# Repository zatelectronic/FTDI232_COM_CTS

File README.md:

<div align="center">

# FTDI232 COM CTS

**Conversor USB-Serial compacto com conector USB-C, chip FT232RL, seleção de tensão 3,3V / 5V, 3 LEDs de status e saída com pino CTS — totalmente SMD**

</div>

---

## 📋 Índice

- [FTDI232 COM CTS](#ftdi232-com-cts)
  - [📋 Índice](#-índice)
  - [Visão Geral](#visão-geral)
  - [Renders 3D](#renders-3d)
  - [Funcionalidades](#funcionalidades)
  - [Diagrama de Blocos](#diagrama-de-blocos)
  - [Especificações Técnicas](#especificações-técnicas)
  - [Lista de Materiais](#lista-de-materiais)
  - [Pinagem dos Conectores](#pinagem-dos-conectores)
    - [J2 — Saída Serial (6 pinos angulado)](#j2--saída-serial-6-pinos-angulado)
    - [JP1 — Seleção de Tensão](#jp1--seleção-de-tensão)
  - [Seleção de Tensão — JP1](#seleção-de-tensão--jp1)
  - [Aplicações](#aplicações)
  - [Estrutura do Repositório](#estrutura-do-repositório)
  - [Como Usar](#como-usar)
    - [Conexão com Arduino (programação)](#conexão-com-arduino-programação)
    - [Conexão com ESP8266 / ESP32](#conexão-com-esp8266--esp32)
    - [Instalação de drivers](#instalação-de-drivers)
  - [Sobre](#sobre)

---

## Visão Geral

**FTDI232 COM CTS** é um módulo conversor **USB para Serial (UART)** compacto e totalmente SMD, projetado pela **ZAT ELECTRONIC** utilizando **KiCad 10**. O módulo é baseado no chip **FT232RL** (SSOP-28), reconhecido automaticamente pelo sistema operacional sem necessidade de drivers adicionais na maioria das plataformas.

O diferencial deste módulo em relação a conversores convencionais é a presença do **pino CTS** no conector de saída de 6 pinos, além do tradicional conjunto **GND / VCC / TX / RX / DTR**. A tensão de saída é selecionável entre **3,3V e 5V** via jumper **(JP1)**, tornando o módulo compatível com uma ampla variedade de microcontroladores e módulos seriais. A entrada USB utiliza o conector **USB-C** (USB4105GFA SMD).

> 💡 Ideal para programação de Arduino bootloader, ESP8266, ESP32 sem USB nativo, módulos GSM, GPS e qualquer dispositivo com interface UART.

---

## Renders 3D

<div align="center">

*Vista superior — FT232RL SSOP-28, USB-C, LEDs SMD 0805, jumper JP1 e conector de 6 pinos com CTS*

<br/>

*Vista isométrica — layout compacto SMD com saída de 6 pinos angulada*

</div>

---

## Funcionalidades

- ✅ **Chip FT232RL** (SSOP-28 SMD) — conversor USB-Serial confiável e amplamente suportado
- ✅ **Conector USB-C** (USB4105GFA SMD) — entrada USB moderna e resistente
- ✅ **Seleção de tensão 3,3V / 5V** via jumper JP1 — compatível com diferentes lógicas
- ✅ **Pino CTS** disponível no conector de saída — diferencial para controle de fluxo
- ✅ **Pino DTR** disponível — reset automático de Arduino e bootloaders
- ✅ **3 LEDs SMD 0805** (L1, L2, L3) — indicação visual de TX, RX e alimentação
- ✅ **Diodo Schottky SS1P3L** (D1, DO-220AA SMD) — proteção na linha de alimentação VBUS
- ✅ **Capacitor eletrolítico 10µF/16V** (C1, EIA-3216 SMD) — filtragem da alimentação
- ✅ **Capacitores de desacoplamento 100nF e 1µF** (C2, C3, C4 — 0805 SMD)
- ✅ **Resistores de proteção e pull-up** (R1–R6 — 1206 SMD)
- ✅ **Layout totalmente SMD** — compacto e profissional
- ✅ **Saída por header de 6 pinos angulado** (J2) — encaixe direto em cabos e módulos

---

## Diagrama de Blocos

```
┌─────────────┐       ┌──────────────────┐       ┌─────────────────────────┐
│  USB-C      │       │   FT232RL        │       │  Conector J2 (6 pinos)  │
│ USB4105GFA  │──────►│   SSOP-28        │──────►│  GND                    │
│             │  USB  │                  │       │  CTS  ← diferencial     │
│  D+ / D-   │       │  TX / RX / DTR   │       │  VCC (3,3V ou 5V)       │
└─────────────┘       │  CTS / RTS       │       │  TX                     │
                      │  CBUS0 / CBUS1   │       │  RX                     │
                      └──────────────────┘       │  DTR                    │
                               │                 └─────────────────────────┘
                          [JP1 Jumper]
                        3,3V ●──○──● 5V
                        (seleção de tensão VCC)

         [L1] TX LED    [L2] RX LED    [L3] PWR LED  ← indicação visual
         [D1] Schottky SS1P3L ← proteção VBUS
```

---

## Especificações Técnicas

| Parâmetro | Valor |
|-----------|-------|
| **Chip conversor** | FT232RL (SSOP-28 SMD) |
| **Conector USB** | USB-C — USB4105GFA SMD |
| **Tensão de saída** | 3,3V ou 5V (selecionável via JP1) |
| **Interface serial** | UART — TX, RX, RTS, CTS, DTR |
| **Pinos disponíveis** | GND, CTS, VCC, TX, RX, DTR |
| **LEDs de status** | 3x SMD 0805 — TX (L1), RX (L2), PWR (L3) |
| **Diodo de proteção** | SS1P3L — Schottky (DO-220AA SMD) |
| **Capacitor principal** | 10µF / 16V (EIA-3216 SMD) |
| **Capacitores de desacoplamento** | 100nF e 1µF (0805 SMD) |
| **Resistores** | 0Ω, 1KΩ, 5,1KΩ (1206 SMD) |
| **Jumper de tensão** | JP1 — 3 pinos 2,54mm (header vertical) |
| **Conector de saída** | J2 — 6 pinos angulado 2,54mm (right angle) |
| **Tipo de montagem** | SMD |
| **Ferramenta de Projeto** | KiCad 10 |

---

## Lista de Materiais

| Ref | Componente | Valor / Parte | Encapsulamento |
|-----|-----------|--------------|----------------|
| U1 | Conversor USB-Serial | FT232RL | SSOP-28 SMD |
| J1 | Conector USB | USB-C (USB4105GFA) | SMD |
| J2 | Conector de Saída | 6 pinos — GND/CTS/VCC/TX/RX/DTR | Header angulado 2,54mm |
| JP1 | Jumper de Tensão | 3,3V / VCC / 5V | Header 3 pinos 2,54mm |
| D1 | Diodo Schottky | SS1P3L | DO-220AA SMD |
| L1 | LED TX | SMD 0805 | 0805 |
| L2 | LED RX | SMD 0805 | 0805 |
| L3 | LED PWR | SMD 0805 | 0805 |
| C1 | Capacitor Eletrolítico | 10µF / 16V | EIA-3216-18 SMD |
| C2, C3 | Capacitor de desacoplamento | 100nF | 0805 SMD |
| C4 | Capacitor de desacoplamento | 1µF / 50V | 0805 SMD |
| R1, R2 | Resistor | 0Ω (jumper) | 1206 SMD |
| R3, R4, R5 | Resistor de proteção | 1KΩ | 1206 SMD |
| R6 | Resistor pull-up | 5,1KΩ | 1206 SMD |

---

## Pinagem dos Conectores

### J2 — Saída Serial (6 pinos angulado)

| Pino | Sinal | Descrição |
|------|-------|-----------|
| 1 | GND | Terra |
| 2 | CTS | Clear To Send — controle de fluxo de hardware |
| 3 | VCC | Tensão de saída (3,3V ou 5V conforme JP1) |
| 4 | TX | Transmissão serial (saída do FT232RL) |
| 5 | RX | Recepção serial (entrada do FT232RL) |
| 6 | DTR | Data Terminal Ready — reset automático Arduino |

### JP1 — Seleção de Tensão

| Posição | Tensão VCC |
|---------|-----------|
| Pinos 1-2 | 3,3V |
| Pinos 2-3 | 5V |

---

## Seleção de Tensão — JP1

O jumper **JP1** define a tensão disponível no pino **VCC** do conector J2:

```
JP1:
  ●──○  ○    →  VCC = 3,3V  (para ESP8266, ESP32, módulos 3,3V)
  ○  ○──●    →  VCC = 5V    (para Arduino Uno, módulos 5V)
```

> ⚠️ Certifique-se de selecionar a tensão correta antes de conectar o dispositivo. Tensão incorreta pode danificar o hardware conectado.

> ℹ️ **CTS (Clear To Send)** é utilizado para controle de fluxo de hardware — o dispositivo conectado sinaliza ao FT232RL que está pronto para receber dados. Ideal para módulos que implementam handshake de hardware.

---

## Aplicações

- 🤖 **Programação de Arduino** — upload de sketches via bootloader com auto-reset pelo DTR
- 📡 **Comunicação com ESP8266 / ESP32** — programação e monitor serial com lógica 3,3V
- 🛰️ **Módulos GPS e GSM** — interface serial para módulos com UART
- 🔧 **Debug serial** — monitoramento de comunicação UART em qualquer dispositivo
- 🏭 **Automação industrial** — interface USB-Serial para equipamentos com RS-232 (com adaptador)
- 💻 **Desenvolvimento embarcado** — substituto compacto de interfaces FTDI comerciais

---

## Estrutura do Repositório

```
FTDI232_COM_CTS/
├── FTDI232.kicad_pro             # Arquivo de projeto KiCad
├── FTDI232.kicad_sch             # Esquemático (KiCad 10)
├── FTDI232.kicad_pcb             # Layout da PCB (KiCad 10)
├── FTDI232.kicad_prl             # Configurações locais do projeto
├── packages3D/                   # Modelos 3D arquivados (STEP / WRL)
│   ├── USB4105GFA.STEP
│   ├── SSOP-28_5.3x10.2mm_P0.65mm.wrl
│   ├── D_SMP_DO-220AA.wrl
│   ├── CP_EIA-3216-18_Kemet-A.wrl
│   ├── LED_0805_2012Metric.wrl
│   ├── R_1206_3216Metric.wrl
│   ├── C_0805_2012Metric.wrl
│   ├── PinHeader_1x03_P2.54mm_Vertical.wrl
│   └── PinHeader_6X1_right.stp
├── fp-info-cache                 # Cache de footprints
├── imagem_1.png                  # Render 3D superior
├── imagem_2.png                  # Render 3D isométrico
└── README.md
```

---

## Como Usar

### Conexão com Arduino (programação)

```
FTDI232 J2          Arduino Uno (header ICSP / Serial)
──────────────      ──────────────────────────────────
GND        ──────►  GND
VCC (5V)   ──────►  5V  (ou VIN)
TX         ──────►  RX  (pino 0)
RX         ──────►  TX  (pino 1)
DTR        ──────►  RESET (via capacitor 100nF)
```

### Conexão com ESP8266 / ESP32

```
FTDI232 J2          ESP8266 / ESP32
──────────────      ─────────────────
GND        ──────►  GND
VCC (3,3V) ──────►  3V3
TX         ──────►  RX
RX         ──────►  TX
CTS        ──────►  (controle de fluxo, opcional)
```

### Instalação de drivers

O **FT232RL** é reconhecido nativamente pela maioria dos sistemas operacionais modernos. Caso necessário, os drivers oficiais estão disponíveis no site do fabricante do chip.

| Sistema Operacional | Driver |
|--------------------|--------|
| Windows 10 / 11 | Automático (Windows Update) ou driver VCP |
| Linux | Nativo (módulo `ftdi_sio`) |
| macOS | Nativo a partir do macOS 10.9+ |

---

## Sobre

<div align="center">

Projetado por **ZAT ELECTRONIC**

*FTDI232 COM CTS — Made in Brazil 🇧🇷*

</div>

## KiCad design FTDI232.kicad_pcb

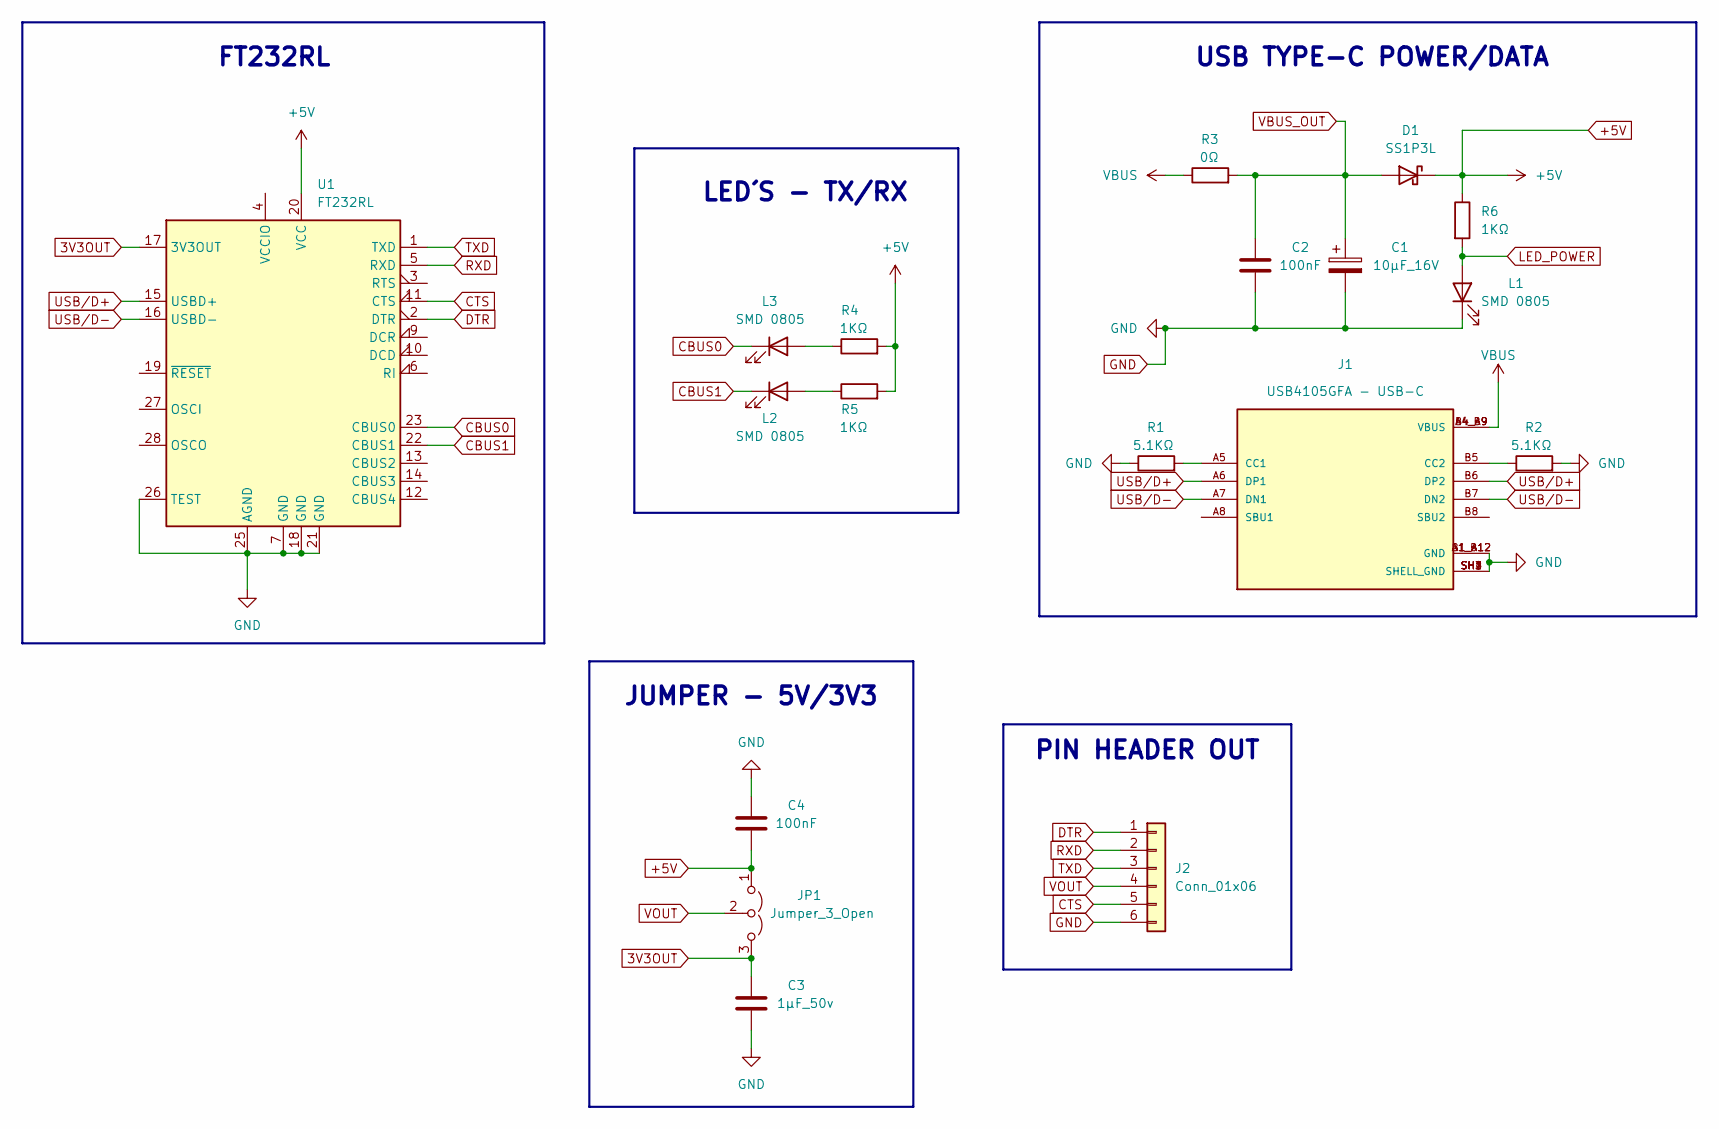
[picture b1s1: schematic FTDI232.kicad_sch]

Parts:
C1: 10μF_16V; CP_EIA-3216-18_Kemet-A
C2, C4: 100nF; C_0805_2012Metric
C3: 1μF_50v; C_0805_2012Metric
D1: SS1P3L; D_SMP_DO-220AA
J1: USB4105GFA - USB-C; USB4105GFA; PARTREV B3
J2: Conn_01x06; PinHeader_1x06_P2.54mm_Vertical
JP1: Jumper_3_Open; PinHeader_1x03_P2.54mm_Vertical
L1, L2, L3: SMD 0805; LED_0805_2012Metric
R1, R2: 5.1KΩ; R_1206_3216Metric
R3: 0Ω; R_1206_3216Metric
R4, R5, R6: 1KΩ; R_1206_3216Metric
U1: FT232RL; SSOP-28_5.3x10.2mm_P0.65mm

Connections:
3V3OUT: C3.2, JP1.3 (B), U1.17 (3V3OUT)
+5V: C4.1, D1.1 (K), JP1.1 (A), R4.2, R5.2, R6.1, U1.20 (VCC)
CBUS0: L3.1 (K), U1.23 (CBUS0)
CBUS1: L2.1 (K), U1.22 (CBUS1)
CTS: J2.5, U1.11 (CTS)
DTR: J2.1, U1.2 (DTR)
GND: C1.2, C2.2, C3.1, C4.2, J1.A1_B12 (GND), J1.B1_A12 (GND), J1.SH1 (SHELL_GND), J1.SH2 (SHELL_GND), J1.SH3 (SHELL_GND), J1.SH4 (SHELL_GND), J2.6, L1.1 (K), R1.1, R2.2, U1.7 (GND), U1.18 (GND), U1.21 (GND), U1.25 (AGND), U1.26 (TEST)
LED_POWER: L1.2 (A), R6.2
unnamed: J1.A5 (CC1), R1.2
unnamed: J1.B5 (CC2), R2.1
unnamed: L2.2 (A), R5.1
unnamed: L3.2 (A), R4.1
RXD: J2.2, U1.5 (RXD)
TXD: J2.3, U1.1 (TXD)
USB/D+: J1.A6 (DP1), J1.B6 (DP2), U1.15 (USBD+)
USB/D-: J1.A7 (DN1), J1.B7 (DN2), U1.16 (USBD-)
VBUS: J1.A4_B9 (VBUS), J1.B4_A9 (VBUS), R3.1
VBUS_OUT: C1.1, C2.1, D1.2 (A), R3.2
VOUT: J2.4, JP1.2 (C)

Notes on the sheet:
FT232RL
JUMPER - 5V/3V3
LED´S - TX/RX
PIN HEADER OUT
USB TYPE-C POWER/DATA

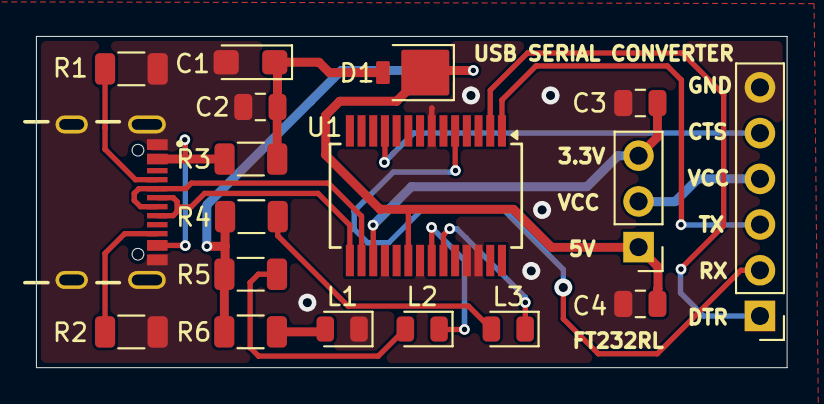
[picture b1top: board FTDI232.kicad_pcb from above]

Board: 2 copper layers, 41.7 x 18.4 mm, 18 parts (0 on the bottom side), 19 nets.

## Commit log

2026-06-28 commit_3
2026-06-29 COMMIT-5
